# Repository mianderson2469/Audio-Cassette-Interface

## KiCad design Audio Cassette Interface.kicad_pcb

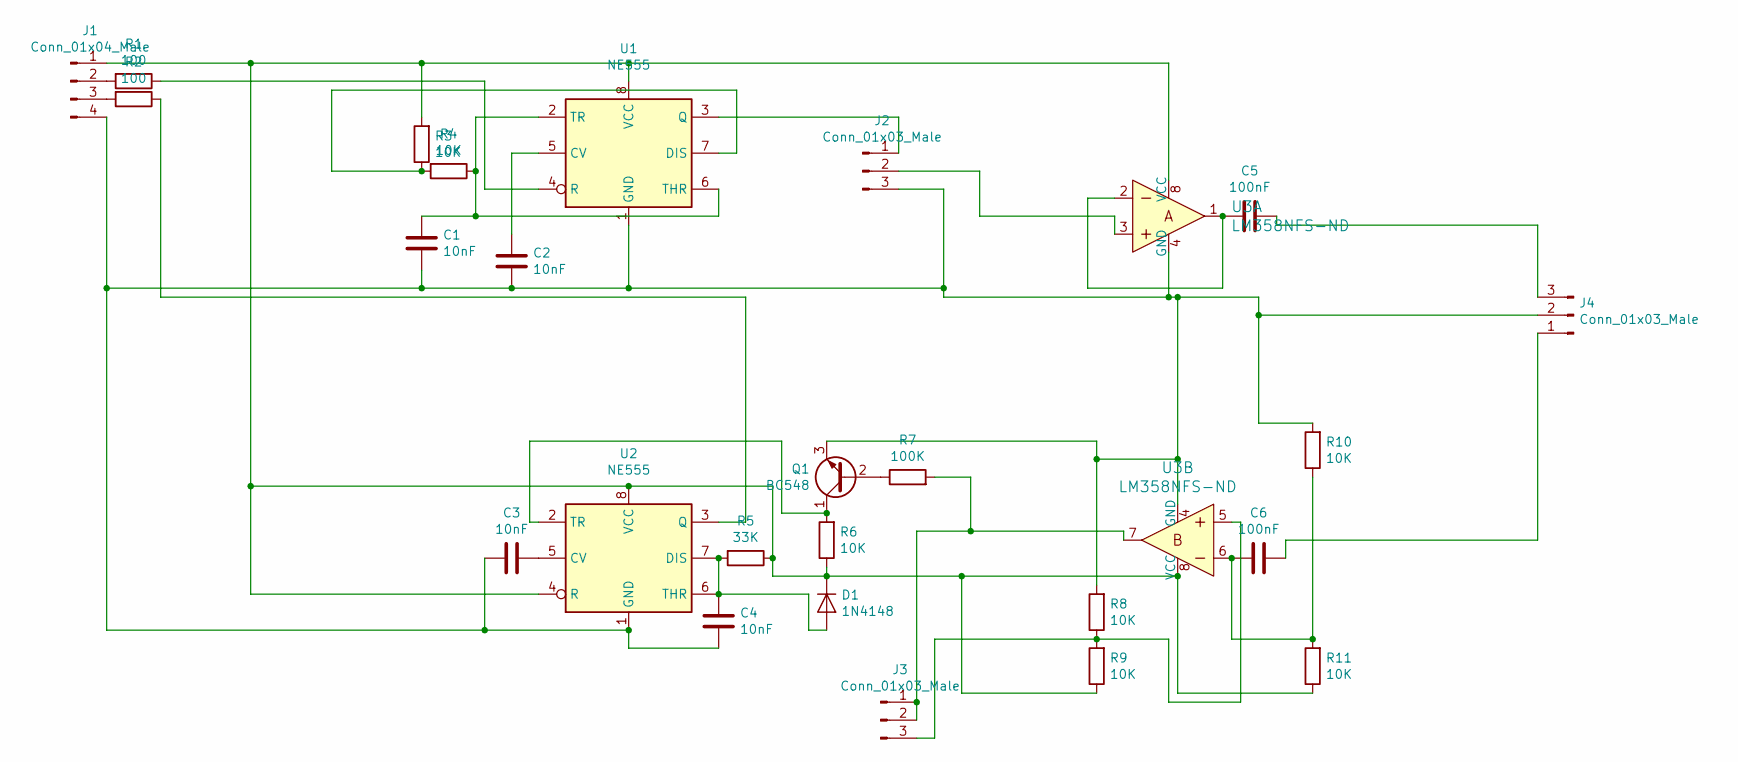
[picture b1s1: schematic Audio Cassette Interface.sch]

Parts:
C1, C2, C3, C4: 10nF; C_Disc_D4.7mm_W2.5mm_P5.00mm
C5, C6: 100nF; C_Disc_D4.7mm_W2.5mm_P5.00mm
D1: 1N4148; D_5W_P5.08mm_Vertical_KathodeUp
J1: Conn_01x04_Male; Molex_MicroClasp_55932-0430_1x04_P2.00mm_Vertical
J2, J3, J4: Conn_01x03_Male; FanPinHeader_1x03_P2.54mm_Vertical
Q1: BC548; TO-92_Inline
R1, R2: 100; R_Axial_DIN0207_L6.3mm_D2.5mm_P5.08mm_Vertical
R3, R4, R6, R8, R9, R10, R11: 10K; R_Axial_DIN0207_L6.3mm_D2.5mm_P5.08mm_Vertical
R5: 33K; R_Axial_DIN0207_L6.3mm_D2.5mm_P5.08mm_Vertical
R7: 100K; R_Axial_DIN0207_L6.3mm_D2.5mm_P5.08mm_Vertical
U1, U2: NE555; DIP-8_W7.62mm_Socket_LongPads
U3: LM358NFS-ND; DIP-8_W7.62mm_LongPads

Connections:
unnamed: C1.1, R4.1, U1.2 (TR), U1.6 (THR)
unnamed: C1.2, C2.1, C3.1, C4.1, J1.4, J2.3, J4.2, Q1.3 (E), R8.2, R10.2, U1.1 (GND), U2.1 (GND), U3.4 (GND)
unnamed: C2.2, U1.5 (CV)
unnamed: C3.2, U2.5 (CV)
unnamed: C4.2, D1.2 (A), R5.2, U2.6 (THR), U2.7 (DIS)
unnamed: C5.1, U3.1, U3.2
unnamed: C5.2, J4.3
unnamed: C6.1, R10.1, R11.2, U3.6
unnamed: C6.2, J4.1
unnamed: D1.1 (K), J1.1, R3.2, R5.1, R6.1, R9.1, R11.1, U1.8 (VCC), U2.4 (R), U2.8 (VCC), U3.8 (VCC)
unnamed: J1.2, R1.2
unnamed: J1.3, R2.2
unnamed: J2.1, U1.3 (Q)
unnamed: J2.2, U3.3
unnamed: J3.1, J3.2, R7.2, U3.7
unnamed: J3.3, R8.1, R9.2, U3.5
unnamed: Q1.1 (C), R6.2, U2.2 (TR)
unnamed: Q1.2 (B), R7.1
unnamed: R1.1, U1.4 (R)
unnamed: R2.1, U2.3 (Q)
unnamed: R3.1, R4.2, U1.7 (DIS)

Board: 2 copper layers, 26 parts (0 on the bottom side), 21 nets, no tracks yet.
